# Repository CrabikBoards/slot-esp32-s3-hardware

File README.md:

# Crabik Slot ESP32-S3 Hardware

Crabik Slot was created so that you can quickly prototype, research and educational projects, because it makes it easy to create and test without having to assemble everything on a breadboard and dig into a pile of wires.

Schematics and board designs (KiCad projects), distributed as open hardware and available under CERN-OHL-W v2 license.

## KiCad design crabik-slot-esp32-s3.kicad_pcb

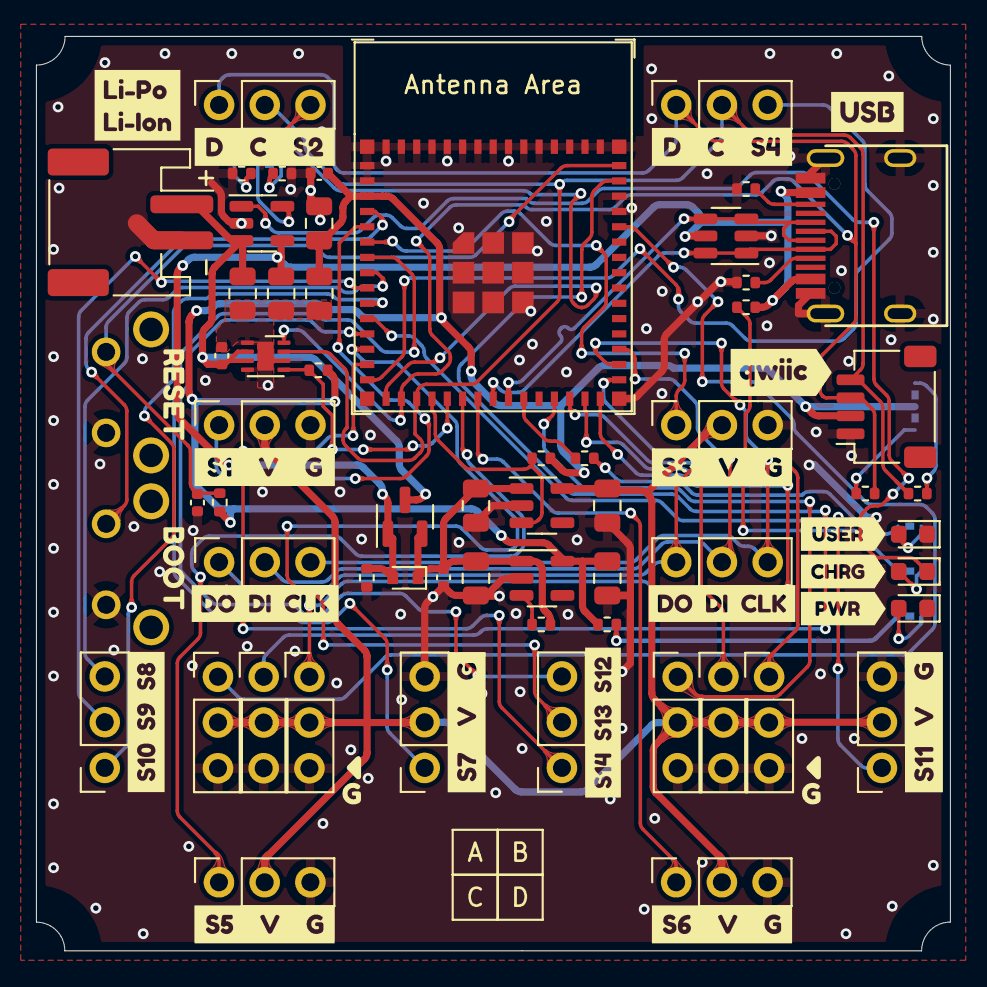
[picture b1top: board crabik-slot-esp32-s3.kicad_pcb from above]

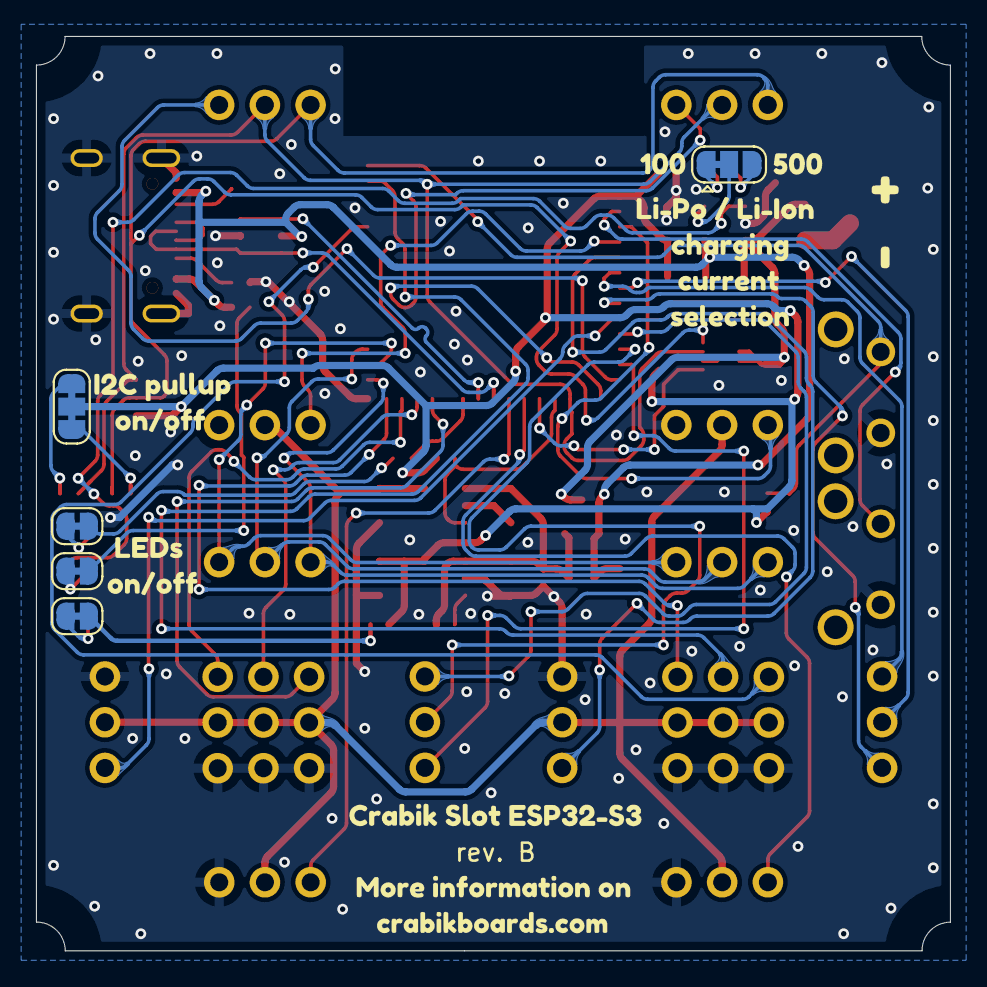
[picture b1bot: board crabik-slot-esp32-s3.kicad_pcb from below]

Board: 2 copper layers, 50.8 x 50.8 mm, 95 parts (13 on the bottom side), 53 nets.

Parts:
C1, C3, C4#2, C6, C9, C10, C11, C12: 10 uF; C_0805_2012Metric
C2, C5: 1 uF; C_0402_1005Metric
C4, C4#3: 100nF; C_0402_1005Metric
D1: MSK4005; D_SOD-523
D2: USER_LED; LED_0603_1608Metric
D3: CHRG_LED; LED_0603_1608Metric
D4: PWR_LED; LED_0603_1608Metric
J1, J1#2, J1#3, J1#4, J1#5, J1#7: UP (A); PinSocket_1x03_P2.54mm_Vertical
J1#6: Battery; JST_PH_S2B-PH-SM4-TB_1x02-1MP_P2.00mm_Horizontal
J2, J2#3: DOWN (A); PinSocket_1x03_P2.54mm_Vertical
J2#2: QWIIC; JST_SH_SM04B-SRSS-TB_1x04-1MP_P1.00mm_Horizontal
J4, J4#2: UP (B); PinSocket_1x03_P2.54mm_Vertical
J5, J5#2: DOWN (B); PinSocket_1x03_P2.54mm_Vertical
J15: CENTER (C) (1); PinHeader_1x03_P2.54mm_Vertical
J16: CENTER (D) (1); PinHeader_1x03_P2.54mm_Vertical
J17: CENTER (C) (2); PinHeader_1x03_P2.54mm_Vertical
J18: CENTER (D) (2); PinHeader_1x03_P2.54mm_Vertical
J19: CENTER (C) (3); PinHeader_1x03_P2.54mm_Vertical
J20: CENTER (D) (3); PinHeader_1x03_P2.54mm_Vertical
JP1: Set charging current; SolderJumper-3_P1.3mm_Bridged12_RoundedPad1.0x1.5mm
JP2: Set I2C Pull-Up; SolderJumper-3_P1.3mm_Bridged12_RoundedPad1.0x1.5mm_копия
JP3: USER_LED on/off; SolderJumper-2_P1.3mm_Bridged_RoundedPad1.0x1.5mm
JP4: CHRG_LED on/off; SolderJumper-2_P1.3mm_Bridged_RoundedPad1.0x1.5mm
JP5: PWR_LED on/off; SolderJumper-2_P1.3mm_Bridged_RoundedPad1.0x1.5mm
P1: USB-C; TYPE-C16PIN
Q1: CJ2301; SOT-23
R1: 10k; R_0402_1005Metric
R2, R4, R12, R13, R14: 5.1 kOhm; R_0402_1005Metric
R3: 2 kOhm; R_0402_1005Metric
R5, R6, R7, R8, R9, R10, R11: 10 kOhm; R_0402_1005Metric
SW1, SW1#2: Reset button; KEY-TH_4P-L7.1-W5.0-P4.50-LS2.5
U1: MCP73831T-2ACI; SOT-23-5
U2: USBLC6-2SC6; SOT-23-6
U3: ESP32-S3-MINI-1
U4: MAX17048; DFN-8-1EP_2x2mm_P0.5mm_EP0.9x1.6mm
U5, U6: RT9080-33GJ5 or AP2112K-3.3; SOT-23-5
kibuzzard-63C28F32: G***; kibuzzard-63C28F32
kibuzzard-63C28786: G***; kibuzzard-63C28786
kibuzzard-63C28790: G***; kibuzzard-63C28790
kibuzzard-63CA6CBF: G***; kibuzzard-63CA6CBF
kibuzzard-63CA6FA5: G***; kibuzzard-63CA6FA5
kibuzzard-63CE9BA7: G***; kibuzzard-63CE9BA7
kibuzzard-63CFAB7C: G***; kibuzzard-63CFAB7C
kibuzzard-63CFAB43: G***; kibuzzard-63CFAB43
kibuzzard-63CFACF8: G***; kibuzzard-63CFACF8
kibuzzard-63CFADAC: G***; kibuzzard-63CFADAC
kibuzzard-63CFAED5: G***; kibuzzard-63CFAED5
kibuzzard-63CFAF5C: G***; kibuzzard-63CFAF5C
kibuzzard-63CFAFAA: G***; kibuzzard-63CFAFAA
kibuzzard-63CFAFDE: G***; kibuzzard-63CFAFDE
kibuzzard-63CFB1DC: G***; kibuzzard-63CFB1DC
kibuzzard-63CFB14C, kibuzzard-63CFB14C#2: G***; kibuzzard-63CFB14C
kibuzzard-63CFB240: G***; kibuzzard-63CFB240
kibuzzard-63CFBBB1, kibuzzard-63CFBBB1#2: G***; kibuzzard-63CFBBB1
kibuzzard-637DF95D: G***; kibuzzard-637DF95D
kibuzzard-637DF950: G***; kibuzzard-637DF950
kibuzzard-637DF968: G***; kibuzzard-637DF968
kibuzzard-637F6C97: G***; kibuzzard-637F6C97
kibuzzard-637F6D25: G***; kibuzzard-637F6D25
kibuzzard-637F6DEA: G***; kibuzzard-637F6DEA
kibuzzard-637F6E06: G***; kibuzzard-637F6E06
kibuzzard-637F66BD: G***; kibuzzard-637F66BD
kibuzzard-637F708F: G***; kibuzzard-637F708F
kibuzzard-637F7041: G***; kibuzzard-637F7041

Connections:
3.3V: C3.1, C4#2.1, C5.1, C12.1, J2#2.2, JP2.2 (C), R1.1, R7.1, R9.2, R14.2, U3.3 (3V3), U6.5 (VOUT)
BATTERY: C4#3.1, C6.1, J1#6.1, Q1.3 (D), U1.3 (VBAT), U4.2 (CELL), U4.3 (VDD)
C: J1.2, J2#2.4, J4#2.2, R11.2, U3.18 (GPIO14/TOUCH14/ADC2_CH3/FSPIWP/FSPIDQS/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), U4.7 (SCL)
CHRG_STAT: D3.1 (K), U1.1 (STAT)
CLK: J1#4.3, J4.3, U3.32 (SPIIO7/GPIO36/FSPICLK/SUBSPICLK)
CS1_S5: J2#3.1, U3.21 (GPIO17/U1TXD/ADC2_CH6)
CS2_S6: J5#2.1, U3.22 (GPIO18/U1RXD/ADC2_CH7/CLK_OUT3)
D: J1.1, J2#2.3, J4#2.1, R8.2, U3.17 (GPIO13/TOUCH13/ADC2_CH2/FSPIQ/FSPIIO7/S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), U4.8 (SDA)
D+: P1.A6 (D+), U2.3 (I/O2), U2.4 (I/O2), U3.24 (GPIO20/U1CTS/ADC2_CH9/CLK_OUT1/USB_D+)
D-: P1.A7 (D-), U2.1 (I/O1), U2.6 (I/O1), U3.23 (GPIO19/U1RTS/ADC2_CH8/CLK_OUT2/USB_D-)
DI: J1#4.2, J4.2, U3.33 (SPIDQS/GPIO37/FSPIQ/SUBSPIQ)
DO: J1#4.1, J4.1, U3.31 (SPIIO6/GPIO35/FSPID/SUBSPID)
EN_TROYKA: R9.1, U3.19 (GPIO15/U0RTS/ADC2_CH4/XTAL_32K_P), U5.3 (EN)
GND: C1.2, C2.2, C3.2, C4.2, C4#2.2, C4#3.2, C5.2, C6.2, C9.2, C10.2, C11.2, C12.2, D2.1 (K), D4.1 (K), J1#2.3, J1#6.2, J1#7.3, J2.3, J2#2.1, J2#3.3, J5.3, J5#2.3, J15.3, J16.3, J17.3, J18.3, J19.3, J20.3, P1.A1 (GND), P1.S1 (SHIELD), R2.2, R3.2, R4.2, R5.2, R6.2, SW1.2, SW1#2.2, U1.2 (VSS), U2.2 (GND), U3.1 (GND), U3.2 (GND), U3.42 (GND), U3.43 (GND), U3.46 (GND), U4.1 (CTG), U4.4 (GND), U4.6 (QSTRT), U4.9 (GND), U5.2 (GND), U6.2 (GND)
LED: R12.2, U3.25 (GPIO21)
LIPO_ALERT: R7.2, U3.20 (GPIO16/U0CTS/ADC2_CH5/XTAL_32K_NH5), U4.5 (ALRT)
unnamed: C2.1, R1.2, SW1#2.1, U3.45 (EN)
unnamed: D2.2 (A), JP3.1 (A)
unnamed: D3.2 (A), JP4.1 (A)
unnamed: D4.2 (A), JP5.1 (A)
unnamed: JP1.1 (A), R5.1
unnamed: JP1.2 (C), U1.5 (PROG)
unnamed: JP1.3 (B), R3.1
unnamed: JP2.1 (A), R11.1
unnamed: JP2.3 (B), R8.1
unnamed: JP3.2 (B), R12.1
unnamed: JP4.2 (B), R13.1
unnamed: JP5.2 (B), R14.1
unnamed: P1.A5 (CC), R4.1
unnamed: P1.B5 (VCONN), R2.1
unnamed: R10.2, U6.3 (EN)
unnamed: SW1.1, U3.4 (GPIO0/BOOT)
RX_S11: J1#2.1, U3.11 (GPIO7/TOUCH7/ADC1_CH6)
S1: J2.1, U3.5 (GPIO1/TOUCH1/ADC1_CH0)
S2: J1.3, U3.16 (GPIO12/TOUCH12/ADC2_CH1/FSPICLK/FSPIIO6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)
S3: J5.1, U3.6 (GPIO2/TOUCH2/ADC1_CH1)
S4: J4#2.3, U3.15 (GPIO11/TOUCH11/ADC2_CH0/FSPID/FSPIIO5/S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)
S7: J1#7.1, U3.7 (GPIO3/TOUCH3/ADC1_CH2)
S8: J1#3.3, U3.8 (GPIO4/TOUCH4/ADC1_CH3)
S9: J1#3.2, U3.9 (GPIO5/TOUCH5/ADC1_CH4)
S10: J1#3.1, U3.10 (GPIO6/TOUCH6/ADC1_CH5)
S13: J1#5.2, U3.13 (GPIO9/TOUCH9/ADC1_CH8/FSPIHD/SUBSPIHD)
S14: J1#5.1, U3.14 (GPIO10/TOUCH10/ADC1_CH9/FSPICS0/FSPIIO4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)
S15: J15.1, U3.41 (GPIO45)
S16: J17.1, U3.44 (GPIO46)
S17: J19.1, U3.30 (GPIO48/SPICLK_N/SUBSPICLK_N_DIFF)
S18: J16.1, U3.27 (GPIO47/SPICLK_P/SUBSPICLK_P_DIFF)
S19: J18.1, U3.28 (SPIIO4/GPIO33/FSPIHD/SUBSPIHD)
S20: J20.1, U3.29 (SPIIO5/GPIO34/FSPICS0/SUBSPICS0)
TX_S12: J1#5.3, U3.12 (GPIO8/TOUCH8/ADC1_CH7/SUBSPICS1)
V: C11.1, J1#2.2, J1#7.2, J2.2, J2#3.2, J5.2, J5#2.2, J15.2, J16.2, J17.2, J18.2, J19.2, J20.2, U5.5 (VOUT)
VBUS: C1.1, D1.2 (A), P1.A4 (VBUS), Q1.1 (G), R6.1, R13.2, U1.4 (VDD), U2.5 (VBUS)
VIN: C4.1, C9.1, C10.1, D1.1 (K), Q1.2 (S), R10.1, U5.1 (VIN), U6.1 (VIN)

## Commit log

2023-02-26 Upload files
